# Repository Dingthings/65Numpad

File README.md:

# 65Numpad
 My first custom keyboard PCB project

*Has several design flaws but it works*
 
 Utilizing detachable numpad with magnetic pogo pins found here
 https://www.aliexpress.com/item/4001222887985.html?spm=a2g0o.cart.0.0.78463c007HJTM9&mp=1

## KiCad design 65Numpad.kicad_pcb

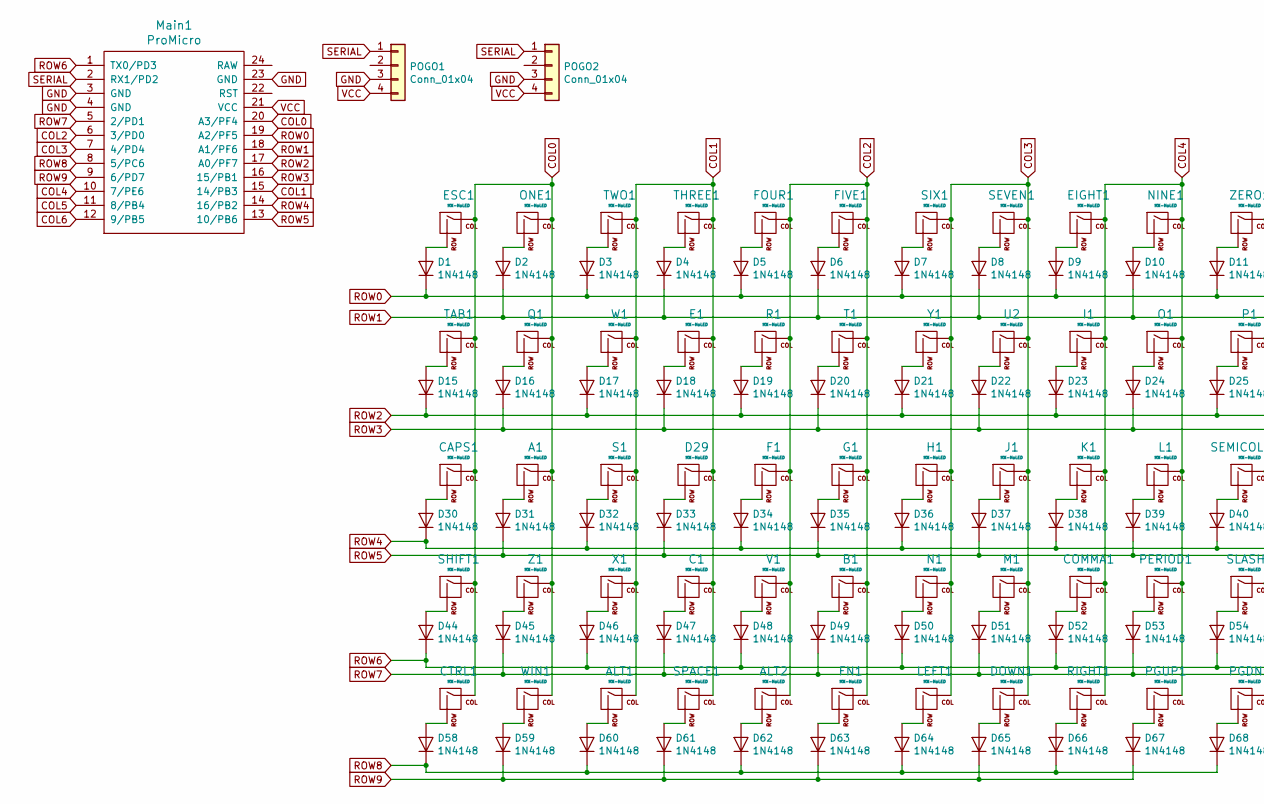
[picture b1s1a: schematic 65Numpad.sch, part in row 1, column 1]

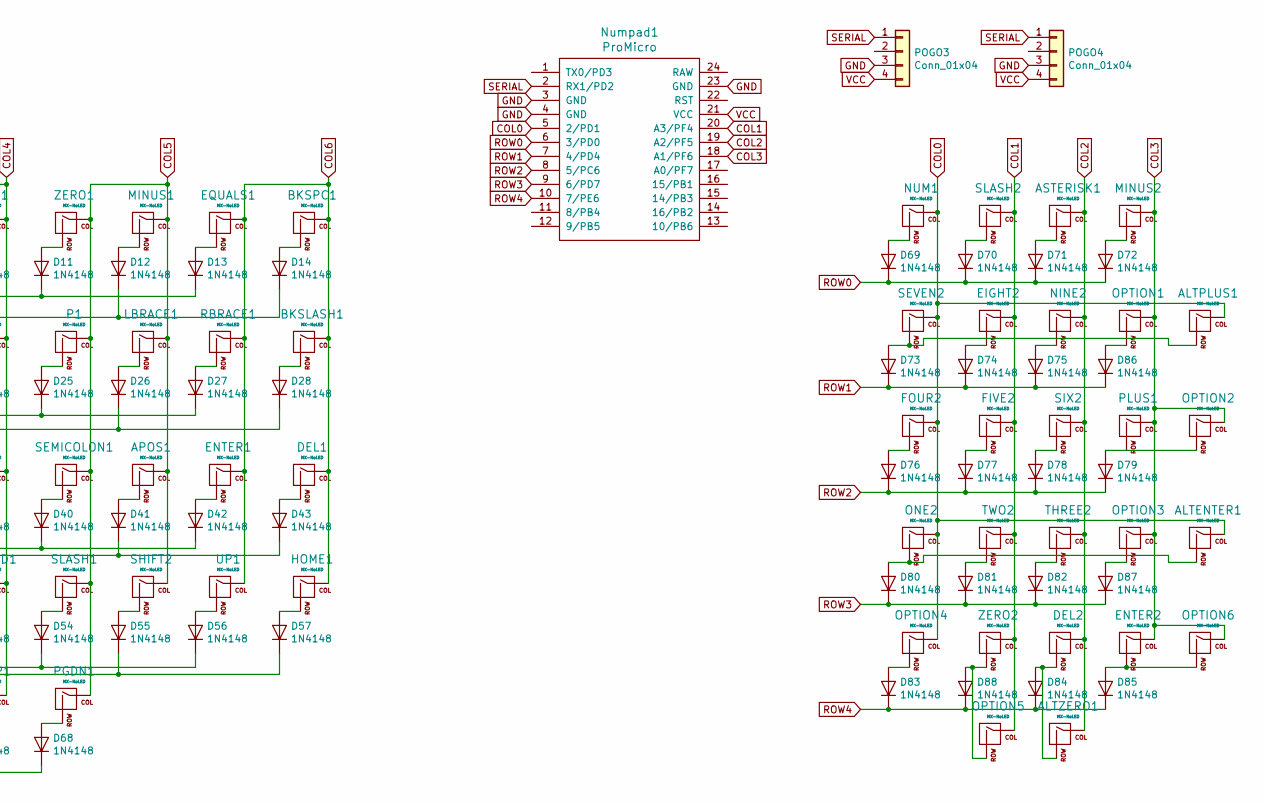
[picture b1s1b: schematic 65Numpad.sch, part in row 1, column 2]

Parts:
A1: MX-NoLED; MXOnly-1U-NoLEDHotswap
ALT1, ALT2: MX-NoLED; MXOnly-1.25U-NoLEDHotswap
ALTENTER1: MX-NoLED; MXOnly-2U-NoLEDHotswap
ALTPLUS1: MX-NoLED; MXOnly-2U-NoLEDHotswap
ALTZERO1: MX-NoLED; MXOnly-2U-ReversedStabilizers-NoLEDHotSwap
APOS1: MX-NoLED; MXOnly-1U-NoLEDHotswap
ASTERISK1: MX-NoLED; MXOnly-1U-NoLEDHotswap
B1: MX-NoLED; MXOnly-1U-NoLEDHotswap
BKSLASH1: MX-NoLED; MXOnly-1.5U-NoLEDHotswap
BKSPC1: MX-NoLED; MXOnly-2U-NoLEDHotswap
C1: MX-NoLED; MXOnly-1U-NoLEDHotswap
CAPS1: MX-NoLED; MXOnly-1.75U-NoLEDHotswap
COMMA1: MX-NoLED; MXOnly-1U-NoLEDHotswap
CTRL1: MX-NoLED; MXOnly-1.25U-NoLEDHotswap
D1, D2, D3, D4, D5, D6, D7, D8, D9, D10, D11, D12, D13, D14, D15, D16, D17, D18, D19, D20, D21, D22, D23, D24, D25, D26, D27, D28, D30, D31, D32, D33, D34, D35, D36, D37, D38, D39, D40, D41, D42, D43, D44, D45, D46, D47, D48, D49, D50, D51, D52, D53, D54, D55, D56, D57, D58, D59, D60, D61, D62, D63, D64, D65, D66, D67, D68, D69, D70, D71, D72, D73, D74, D75, D76, D77, D78, D79, D80, D81, D82, D83, D84, D85, D86, D87, D88: 1N4148; D_DO-35_SOD27_P7.62mm_Horizontal
D29: MX-NoLED; MXOnly-1U-NoLEDHotswap
DEL1, DEL2: MX-NoLED; MXOnly-1U-NoLEDHotswap
DOWN1: MX-NoLED; MXOnly-1U-NoLEDHotswap
E1: MX-NoLED; MXOnly-1U-NoLEDHotswap
EIGHT1, EIGHT2: MX-NoLED; MXOnly-1U-NoLEDHotswap
ENTER1: MX-NoLED; MXOnly-2.25U-NoLEDHotswap
ENTER2: MX-NoLED; MXOnly-2U-ReversedStabilizers-NoLEDHotSwap
EQUALS1: MX-NoLED; MXOnly-1U-NoLEDHotswap
ESC1: MX-NoLED; MXOnly-1U-NoLEDHotswap
F1: MX-NoLED; MXOnly-1U-NoLEDHotswap
FIVE1, FIVE2: MX-NoLED; MXOnly-1U-NoLEDHotswap
FN1: MX-NoLED; MXOnly-1.25U-NoLEDHotswap
FOUR1, FOUR2: MX-NoLED; MXOnly-1U-NoLEDHotswap
G1: MX-NoLED; MXOnly-1U-NoLEDHotswap
H1: MX-NoLED; MXOnly-1U-NoLEDHotswap
HOME1: MX-NoLED; MXOnly-1U-NoLEDHotswap
I1: MX-NoLED; MXOnly-1U-NoLEDHotswap
J1: MX-NoLED; MXOnly-1U-NoLEDHotswap
K1: MX-NoLED; MXOnly-1U-NoLEDHotswap
L1: MX-NoLED; MXOnly-1U-NoLEDHotswap
LBRACE1: MX-NoLED; MXOnly-1U-NoLEDHotswap
LEFT1: MX-NoLED; MXOnly-1U-NoLEDHotswap
M1: MX-NoLED; MXOnly-1U-NoLEDHotswap
MINUS1, MINUS2: MX-NoLED; MXOnly-1U-NoLEDHotswap
Main1: ProMicro; ArduinoProMicro
N1: MX-NoLED; MXOnly-1U-NoLEDHotswap
NINE1, NINE2: MX-NoLED; MXOnly-1U-NoLEDHotswap
NUM1: MX-NoLED; MXOnly-1U-NoLEDHotswap
Numpad1: ProMicro; ArduinoProMicro
O1: MX-NoLED; MXOnly-1U-NoLEDHotswap
ONE1, ONE2: MX-NoLED; MXOnly-1U-NoLEDHotswap
OPTION1, OPTION2, OPTION3, OPTION4, OPTION5, OPTION6: MX-NoLED; MXOnly-1U-NoLEDHotswap
P1: MX-NoLED; MXOnly-1U-NoLEDHotswap
PERIOD1: MX-NoLED; MXOnly-1U-NoLEDHotswap
PGDN1: MX-NoLED; MXOnly-1U-NoLEDHotswap
PGUP1: MX-NoLED; MXOnly-1U-NoLEDHotswap
PLUS1: MX-NoLED; MXOnly-2U-ReversedStabilizers-NoLEDHotSwap
POGO1, POGO3: Conn_01x04; PogoConnector
POGO2, POGO4: Conn_01x04; PogoConnectorMirrored
Q1: MX-NoLED; MXOnly-1U-NoLEDHotswap
R1: MX-NoLED; MXOnly-1U-NoLEDHotswap
RBRACE1: MX-NoLED; MXOnly-1U-NoLEDHotswap
RIGHT1: MX-NoLED; MXOnly-1U-NoLEDHotswap
S1: MX-NoLED; MXOnly-1U-NoLEDHotswap
SEMICOLON1: MX-NoLED; MXOnly-1U-NoLEDHotswap
SEVEN1, SEVEN2: MX-NoLED; MXOnly-1U-NoLEDHotswap
SHIFT1: MX-NoLED; MXOnly-2.25U-NoLEDHotswap
SHIFT2: MX-NoLED; MXOnly-1.75U-NoLEDHotswap
SIX1, SIX2: MX-NoLED; MXOnly-1U-NoLEDHotswap
SLASH1, SLASH2: MX-NoLED; MXOnly-1U-NoLEDHotswap
SPACE1: MX-NoLED; MXOnly-6.25U-ReversedStabilizers-NoLEDHotswap
T1: MX-NoLED; MXOnly-1U-NoLEDHotswap
TAB1: MX-NoLED; MXOnly-1.5U-NoLEDHotswap
THREE1, THREE2: MX-NoLED; MXOnly-1U-NoLEDHotswap
TWO1, TWO2: MX-NoLED; MXOnly-1U-NoLEDHotswap
U2: MX-NoLED; MXOnly-1U-NoLEDHotswap
UP1: MX-NoLED; MXOnly-1U-NoLEDHotswap
V1: MX-NoLED; MXOnly-1U-NoLEDHotswap
W1: MX-NoLED; MXOnly-1U-NoLEDHotswap
WIN1: MX-NoLED; MXOnly-1.25U-NoLEDHotswap
X1: MX-NoLED; MXOnly-1U-NoLEDHotswap
Y1: MX-NoLED; MXOnly-1U-NoLEDHotswap
Z1: MX-NoLED; MXOnly-1U-NoLEDHotswap
ZERO1: MX-NoLED; MXOnly-1U-NoLEDHotswap
ZERO2: MX-NoLED; MXOnly-2U-ReversedStabilizers-NoLEDHotSwap

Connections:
COL0: A1.1 (COL), ALTENTER1.1 (COL), ALTPLUS1.1 (COL), CAPS1.1 (COL), CTRL1.1 (COL), ESC1.1 (COL), FOUR2.1 (COL), Main1.20 (A3/PF4), NUM1.1 (COL), Numpad1.5 (2/PD1), ONE1.1 (COL), ONE2.1 (COL), OPTION4.1 (COL), Q1.1 (COL), SEVEN2.1 (COL), SHIFT1.1 (COL), TAB1.1 (COL), WIN1.1 (COL), Z1.1 (COL); also elsewhere on the board
COL1: ALT1.1 (COL), C1.1 (COL), D29.1 (COL), E1.1 (COL), EIGHT2.1 (COL), FIVE2.1 (COL), Main1.15 (14/PB3), Numpad1.20 (A3/PF4), OPTION5.1 (COL), S1.1 (COL), SLASH2.1 (COL), SPACE1.1 (COL), THREE1.1 (COL), TWO1.1 (COL), TWO2.1 (COL), W1.1 (COL), X1.1 (COL), ZERO2.1 (COL); also elsewhere on the board
COL2: ALT2.1 (COL), ALTZERO1.1 (COL), ASTERISK1.1 (COL), B1.1 (COL), DEL2.1 (COL), F1.1 (COL), FIVE1.1 (COL), FN1.1 (COL), FOUR1.1 (COL), G1.1 (COL), Main1.6 (3/PD0), NINE2.1 (COL), Numpad1.19 (A2/PF5), R1.1 (COL), SIX2.1 (COL), T1.1 (COL), THREE2.1 (COL), V1.1 (COL); also elsewhere on the board
COL3: DOWN1.1 (COL), ENTER2.1 (COL), H1.1 (COL), J1.1 (COL), LEFT1.1 (COL), M1.1 (COL), MINUS2.1 (COL), Main1.7 (4/PD4), N1.1 (COL), Numpad1.18 (A1/PF6), OPTION1.1 (COL), OPTION2.1 (COL), OPTION3.1 (COL), OPTION6.1 (COL), PLUS1.1 (COL), SEVEN1.1 (COL), SIX1.1 (COL), U2.1 (COL), Y1.1 (COL); also elsewhere on the board
COL4: COMMA1.1 (COL), EIGHT1.1 (COL), I1.1 (COL), K1.1 (COL), L1.1 (COL), Main1.10 (7/PE6), NINE1.1 (COL), O1.1 (COL), PERIOD1.1 (COL), PGUP1.1 (COL), RIGHT1.1 (COL)
COL5: APOS1.1 (COL), LBRACE1.1 (COL), MINUS1.1 (COL), Main1.11 (8/PB4), P1.1 (COL), PGDN1.1 (COL), SEMICOLON1.1 (COL), SHIFT2.1 (COL), SLASH1.1 (COL), ZERO1.1 (COL)
COL6: BKSLASH1.1 (COL), BKSPC1.1 (COL), DEL1.1 (COL), ENTER1.1 (COL), EQUALS1.1 (COL), HOME1.1 (COL), Main1.12 (9/PB5), RBRACE1.1 (COL), UP1.1 (COL)
GND: Main1.3 (GND), Main1.4 (GND), Main1.23 (GND), Numpad1.3 (GND), Numpad1.4 (GND), Numpad1.23 (GND), POGO1.3, POGO2.3, POGO3.3, POGO4.3
unnamed: A1.2 (ROW), D31.2 (A)
unnamed: ALT1.2 (ROW), D60.2 (A)
unnamed: ALT2.2 (ROW), D62.2 (A)
unnamed: ALTENTER1.2 (ROW), D80.2 (A), ONE2.2 (ROW)
unnamed: ALTPLUS1.2 (ROW), D73.2 (A), SEVEN2.2 (ROW)
unnamed: ALTZERO1.2 (ROW), D84.2 (A), DEL2.2 (ROW)
unnamed: APOS1.2 (ROW), D41.2 (A)
unnamed: ASTERISK1.2 (ROW), D71.2 (A)
unnamed: B1.2 (ROW), D49.2 (A)
unnamed: BKSLASH1.2 (ROW), D28.2 (A)
unnamed: BKSPC1.2 (ROW), D14.2 (A)
unnamed: C1.2 (ROW), D47.2 (A)
unnamed: CAPS1.2 (ROW), D30.2 (A)
unnamed: COMMA1.2 (ROW), D52.2 (A)
unnamed: CTRL1.2 (ROW), D58.2 (A)
unnamed 23: D1.2 (A), ESC1.2 (ROW); also elsewhere on the board
unnamed 24: D2.2 (A), ONE1.2 (ROW); also elsewhere on the board
unnamed 25: D3.2 (A), TWO1.2 (ROW); also elsewhere on the board
unnamed 26: D4.2 (A), THREE1.2 (ROW); also elsewhere on the board
unnamed 27: D5.2 (A), FOUR1.2 (ROW); also elsewhere on the board
unnamed 28: D6.2 (A), FIVE1.2 (ROW); also elsewhere on the board
unnamed 29: D7.2 (A), SIX1.2 (ROW); also elsewhere on the board
unnamed: D8.2 (A), SEVEN1.2 (ROW)
unnamed: D9.2 (A), EIGHT1.2 (ROW)
unnamed: D10.2 (A), NINE1.2 (ROW)
unnamed: D11.2 (A), ZERO1.2 (ROW)
unnamed: D12.2 (A), MINUS1.2 (ROW)
unnamed: D13.2 (A), EQUALS1.2 (ROW)
unnamed: D15.2 (A), TAB1.2 (ROW)
unnamed: D16.2 (A), Q1.2 (ROW)
unnamed: D17.2 (A), W1.2 (ROW)
unnamed: D18.2 (A), E1.2 (ROW)
unnamed: D19.2 (A), R1.2 (ROW)
unnamed: D20.2 (A), T1.2 (ROW)
unnamed: D21.2 (A), Y1.2 (ROW)
unnamed: D22.2 (A), U2.2 (ROW)
unnamed: D23.2 (A), I1.2 (ROW)
unnamed: D24.2 (A), O1.2 (ROW)
unnamed: D25.2 (A), P1.2 (ROW)
unnamed: D26.2 (A), LBRACE1.2 (ROW)
unnamed: D27.2 (A), RBRACE1.2 (ROW)
unnamed: D29.2 (ROW), D33.2 (A)
unnamed: D32.2 (A), S1.2 (ROW)
unnamed: D34.2 (A), F1.2 (ROW)
unnamed: D35.2 (A), G1.2 (ROW)
unnamed: D36.2 (A), H1.2 (ROW)
unnamed: D37.2 (A), J1.2 (ROW)
unnamed: D38.2 (A), K1.2 (ROW)
unnamed: D39.2 (A), L1.2 (ROW)
unnamed: D40.2 (A), SEMICOLON1.2 (ROW)
unnamed: D42.2 (A), ENTER1.2 (ROW)
unnamed: D43.2 (A), DEL1.2 (ROW)
unnamed: D44.2 (A), SHIFT1.2 (ROW)
unnamed: D45.2 (A), Z1.2 (ROW)
unnamed: D46.2 (A), X1.2 (ROW)
unnamed: D48.2 (A), V1.2 (ROW)
unnamed: D50.2 (A), N1.2 (ROW)
unnamed: D51.2 (A), M1.2 (ROW)
unnamed: D53.2 (A), PERIOD1.2 (ROW)
unnamed: D54.2 (A), SLASH1.2 (ROW)
unnamed: D55.2 (A), SHIFT2.2 (ROW)
unnamed: D56.2 (A), UP1.2 (ROW)
unnamed: D57.2 (A), HOME1.2 (ROW)
unnamed: D59.2 (A), WIN1.2 (ROW)
unnamed: D61.2 (A), SPACE1.2 (ROW)
unnamed: D63.2 (A), FN1.2 (ROW)
unnamed: D64.2 (A), LEFT1.2 (ROW)
unnamed: D65.2 (A), DOWN1.2 (ROW)
unnamed: D66.2 (A), RIGHT1.2 (ROW)
unnamed: D67.2 (A), PGUP1.2 (ROW)
unnamed: D68.2 (A), PGDN1.2 (ROW)
unnamed: D69.2 (A), NUM1.2 (ROW)
unnamed: D70.2 (A), SLASH2.2 (ROW)
unnamed: D72.2 (A), MINUS2.2 (ROW)
unnamed: D74.2 (A), EIGHT2.2 (ROW)
unnamed: D75.2 (A), NINE2.2 (ROW)
unnamed: D76.2 (A), FOUR2.2 (ROW)
unnamed: D77.2 (A), FIVE2.2 (ROW)
unnamed: D78.2 (A), SIX2.2 (ROW)
unnamed: D79.2 (A), OPTION2.2 (ROW), PLUS1.2 (ROW)
unnamed: D81.2 (A), TWO2.2 (ROW)
unnamed: D82.2 (A), THREE2.2 (ROW)
unnamed: D83.2 (A), OPTION4.2 (ROW)
unnamed: D85.2 (A), ENTER2.2 (ROW), OPTION6.2 (ROW)
unnamed: D86.2 (A), OPTION1.2 (ROW)
unnamed: D87.2 (A), OPTION3.2 (ROW)
unnamed: D88.2 (A), OPTION5.2 (ROW), ZERO2.2 (ROW)
ROW0: D1.1 (K), D3.1 (K), D5.1 (K), D7.1 (K), D9.1 (K), D11.1 (K), D13.1 (K), D69.1 (K), D70.1 (K), D71.1 (K), D72.1 (K), Main1.19 (A2/PF5), Numpad1.6 (3/PD0)
ROW1: D2.1 (K), D4.1 (K), D6.1 (K), D8.1 (K), D10.1 (K), D12.1 (K), D14.1 (K), D73.1 (K), D74.1 (K), D75.1 (K), D86.1 (K), Main1.18 (A1/PF6), Numpad1.7 (4/PD4)
ROW2: D15.1 (K), D17.1 (K), D19.1 (K), D21.1 (K), D23.1 (K), D25.1 (K), D27.1 (K), D76.1 (K), D77.1 (K), D78.1 (K), D79.1 (K), Main1.17 (A0/PF7), Numpad1.8 (5/PC6)
ROW3: D16.1 (K), D18.1 (K), D20.1 (K), D22.1 (K), D24.1 (K), D26.1 (K), D28.1 (K), D80.1 (K), D81.1 (K), D82.1 (K), D87.1 (K), Main1.16 (15/PB1), Numpad1.9 (6/PD7)
ROW4: D30.1 (K), D32.1 (K), D34.1 (K), D36.1 (K), D38.1 (K), D40.1 (K), D42.1 (K), D83.1 (K), D84.1 (K), D85.1 (K), D88.1 (K), Main1.14 (16/PB2), Numpad1.10 (7/PE6)
ROW5: D31.1 (K), D33.1 (K), D35.1 (K), D37.1 (K), D39.1 (K), D41.1 (K), D43.1 (K), Main1.13 (10/PB6)
ROW6: D44.1 (K), D46.1 (K), D48.1 (K), D50.1 (K), D52.1 (K), D54.1 (K), D56.1 (K), Main1.1 (TX0/PD3)
ROW7: D45.1 (K), D47.1 (K), D49.1 (K), D51.1 (K), D53.1 (K), D55.1 (K), D57.1 (K), Main1.5 (2/PD1)
ROW8: D58.1 (K), D60.1 (K), D62.1 (K), D64.1 (K), D66.1 (K), D68.1 (K), Main1.8 (5/PC6)
ROW9: D59.1 (K), D61.1 (K), D63.1 (K), D65.1 (K), D67.1 (K), Main1.9 (6/PD7)
SERIAL: Main1.2 (RX1/PD2), Numpad1.2 (RX1/PD2), POGO1.1, POGO2.1, POGO3.1, POGO4.1
VCC: Main1.21 (VCC), Numpad1.21 (VCC), POGO1.4, POGO2.4, POGO3.4, POGO4.4

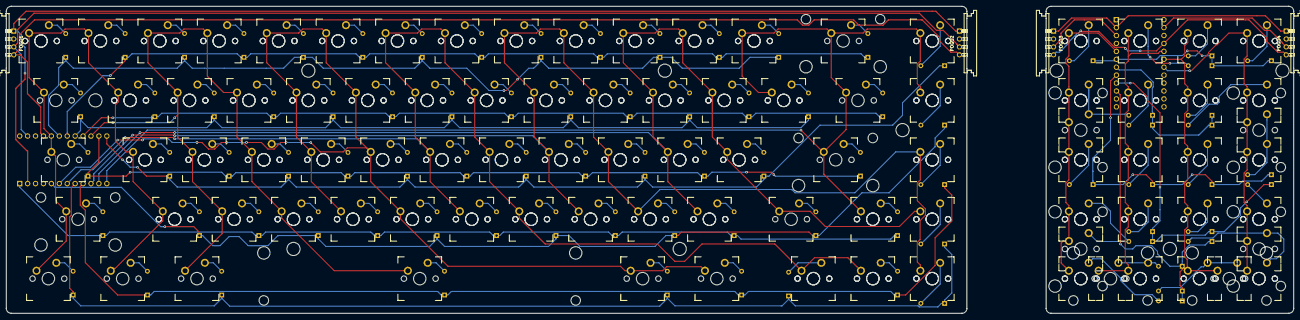
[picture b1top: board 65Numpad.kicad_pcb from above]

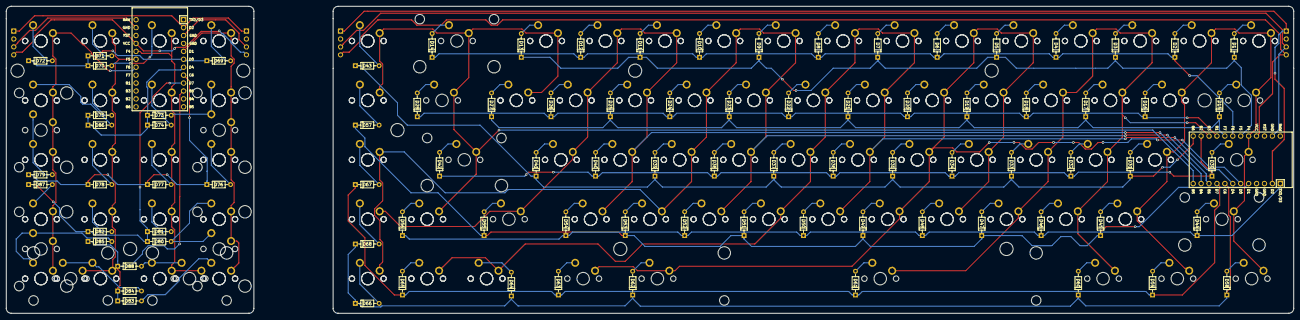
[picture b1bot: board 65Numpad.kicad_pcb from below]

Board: 2 copper layers, 412.8 x 98.4 mm, 186 parts (87 on the bottom side), 107 nets.

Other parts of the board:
ESC: MX-NoLED; MXOnly-1U-NoLEDHotswap
FIVE: MX-NoLED; MXOnly-1U-NoLEDHotswap
FOUR: MX-NoLED; MXOnly-1U-NoLEDHotswap
ONE: MX-NoLED; MXOnly-1U-NoLEDHotswap
SIX: MX-NoLED; MXOnly-1U-NoLEDHotswap
THREE: MX-NoLED; MXOnly-1U-NoLEDHotswap
TWO: MX-NoLED; MXOnly-1U-NoLEDHotswap

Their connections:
COL0: ESC.1, ONE.1; also elsewhere on the board
COL1: THREE.1, TWO.1; also elsewhere on the board
COL2: FIVE.1, FOUR.1; also elsewhere on the board
COL3: SIX.1; also elsewhere on the board
unnamed 23: ESC.2; also elsewhere on the board
unnamed 24: ONE.2; also elsewhere on the board
unnamed 25: TWO.2; also elsewhere on the board
unnamed 26: THREE.2; also elsewhere on the board
unnamed 27: FOUR.2; also elsewhere on the board
unnamed 28: FIVE.2; also elsewhere on the board
unnamed 29: SIX.2; also elsewhere on the board

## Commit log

2020-12-31 created project
2020-12-31 Add submodules
2020-12-31 Component submodules
2020-12-31 Create sym-lib-table
2020-12-31 Type C submodule
2020-12-31 More submodules
2020-12-31 added symbols
2020-12-31 Matrix setup
2020-12-31 Duplex Matrix
2021-01-01 Assign footprints
2021-01-01 Finished assigning footprints
2021-01-01 Keebio bugged
2021-01-01 Arranged PCB
2021-01-03 Almost done routing
2021-01-03 Finished routing
2021-01-04 Routed numpad
2021-01-04 Changed footprint to double sided hot swap
2021-01-04 Adjusted positions
2021-01-12 Pogo adjustments
2021-01-24 Removed traces
2021-01-24 Schematic 1u addons
2021-01-24 Rerouted
2021-01-24 Double checking tracks
2021-01-25 PCB adjustments
2021-01-26 Silkscreen changes
2021-01-30 Created FR4 plate
2021-02-01 Forgot the solder mask :(
2021-04-19 Create STLs
2021-04-19 Create files here
